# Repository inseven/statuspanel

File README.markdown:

# StatusPanel

eInk desk calendar and status board

## Overview

StatusPanel is a modern take on the desk calendar. It shows you just what you need to know about your upcoming day, without the temptation of messages, social media feeds, or the other online distractions that come from checking your phone.

Content is curated through an iOS app, meaning your StatusPanel can show events from any of the calendars you have on your phone, without sharing that content to any third-party service.

### Content Sources

The StatusPanel iOS app has built-in support for a number of content sources:

- Calendar
- [London Underground](https://tfl.gov.uk/modes/tube/) (UK)
- [National Rail](https://www.nationalrail.co.uk) (UK)
- [ZenQuotes](https://zenquotes.io)

### Privacy

StatusPanel uses end-to-end encryption to ensure your data remains private to you. Keys exchanged directly between StatusPanel and your phone are used to encrypt all updates; no one but you can see your updates.

StatusPanel can optionally show a privacy image or redact content at the touch of a button if you're worried who might see your calendar.

### Getting StatusPanel

StatusPanel is an open source project in the fairly early stages of development. We're planning to submit our [iOS app](ios/README,markdown) to the app store in the coming months and would love to manufacture a small batch of PCBs to make it easy for people to assemble their own. (It's 2021 though, so that might take longer than usual.)

If you can't wait to try it out, have a little technical experience, and don't mind getting your hands dirty, check out the [device documentation](device/README.markdown) for part listings and PCB schematics. If something's not clear, please reach out; we're happy to help out where we can and always appreciate code and documentation [contributions](#contributing) big or small.

## Technical Details

### Components

StatusPanel comprises a number of different components:

- [Firmware](firmware/README.markdown)
- [Device](device/README.markdown)
- [iOS app](ios/README.markdown)
- [Service](service/README.markdown)

## Development

### Installing Dependencies

StatusPanel uses [Git Submodules](https://git-scm.com/book/en/v2/Git-Tools-Submodules), so before doing anything else, you'll need to do:

```bash
git submodule update --init --recursive
```

N.B. You'll also need to run this command if the submodules change.

Once your submodules are up-to-date, you can install the dependencies for all StatusPanel components using the `install-dependencies.sh` script:

```bash
scripts/install-dependencies.sh
```

This script installs all dependencies in the `.local` folder within the project root, does not require root, and should not impact your local machine configuration. Scripts that rely on these dependencies source the `scripts/environment.sh` script which configures the path at runtime.

## Contributing

We invite and welcome contributions! There's a pretty comprehensive list of [issues](https://github.com/inseven/statuspanel/issues) to get you started, and our documentation is always in need of some care and attention.

Please recognise StatusPanel is a labour of love, and be respectful of others in your communications. We will not accept racism, sexism, or any form of discrimination in our community.

## Licensing

StatusPanel is licensed under the MIT License (see [LICENSE](LICENSE)).

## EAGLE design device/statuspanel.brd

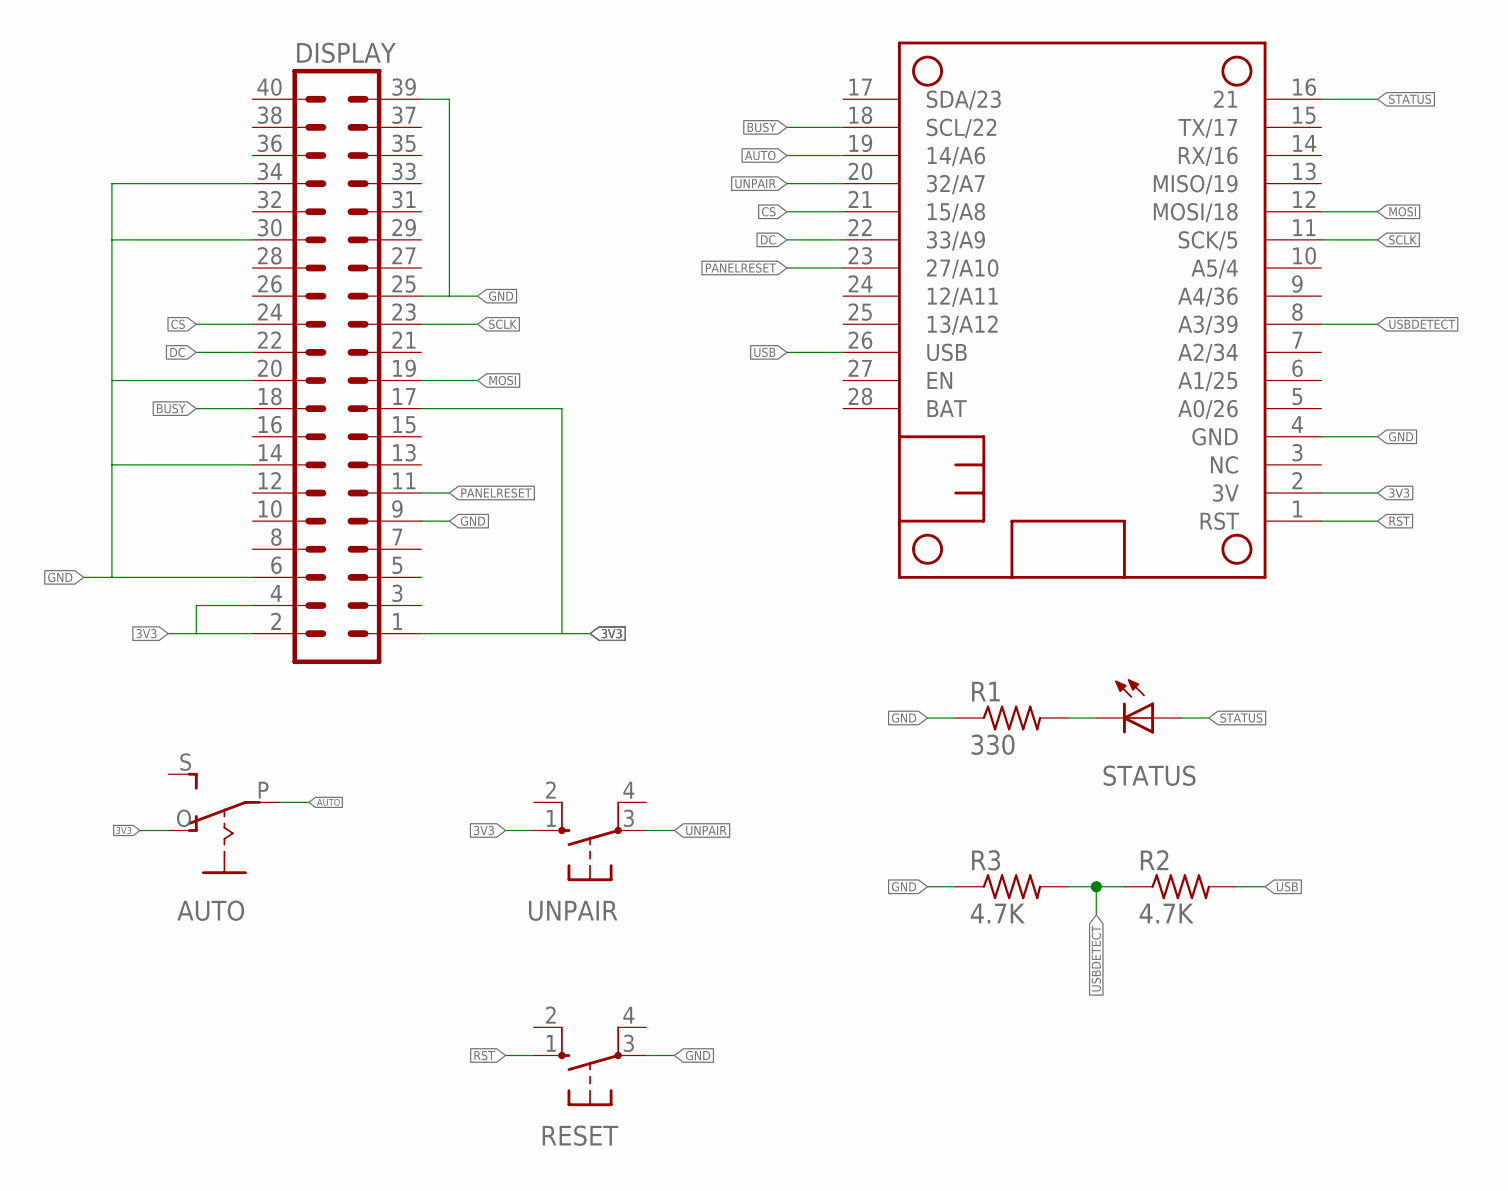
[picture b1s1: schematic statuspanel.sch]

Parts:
AUTO: EG1218S; EG1218
DISPLAY: MA20-2
HUZZAH32: HUZZAH32_NODIM; FEATHERWING_DIM
R1: 330; R0805
R2, R3: 4.7K; R0805
RESET: 10-XX; B3F-10XX
STATUS: LED3MM
UNPAIR: 10-XX; B3F-10XX

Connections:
3V3: AUTO.O, DISPLAY.1, DISPLAY.2, DISPLAY.4, DISPLAY.17, HUZZAH32.2 (3V), UNPAIR.1 (S)
AUTO: AUTO.P, HUZZAH32.19 (14/A6)
BUSY: DISPLAY.18, HUZZAH32.18 (SCL/22)
CS: DISPLAY.24, HUZZAH32.21 (15/A8)
DC: DISPLAY.22, HUZZAH32.22 (33/A9)
GND: DISPLAY.6, DISPLAY.9, DISPLAY.14, DISPLAY.20, DISPLAY.25, DISPLAY.30, DISPLAY.34, DISPLAY.39, HUZZAH32.4 (GND), R1.1, R3.1, RESET.3
MOSI: DISPLAY.19, HUZZAH32.12 (MOSI/18)
unnamed: R1.2, STATUS.K (C)
PANELRESET: DISPLAY.11, HUZZAH32.23 (27/A10)
RST: HUZZAH32.1 (RST), RESET.1 (S)
SCLK: DISPLAY.23, HUZZAH32.11 (SCK/5)
STATUS: HUZZAH32.16 (21), STATUS.A
UNPAIR: HUZZAH32.20 (32/A7), UNPAIR.3
USB: HUZZAH32.26 (USB), R2.2
USBDETECT: HUZZAH32.8 (A3/39), R2.1, R3.2

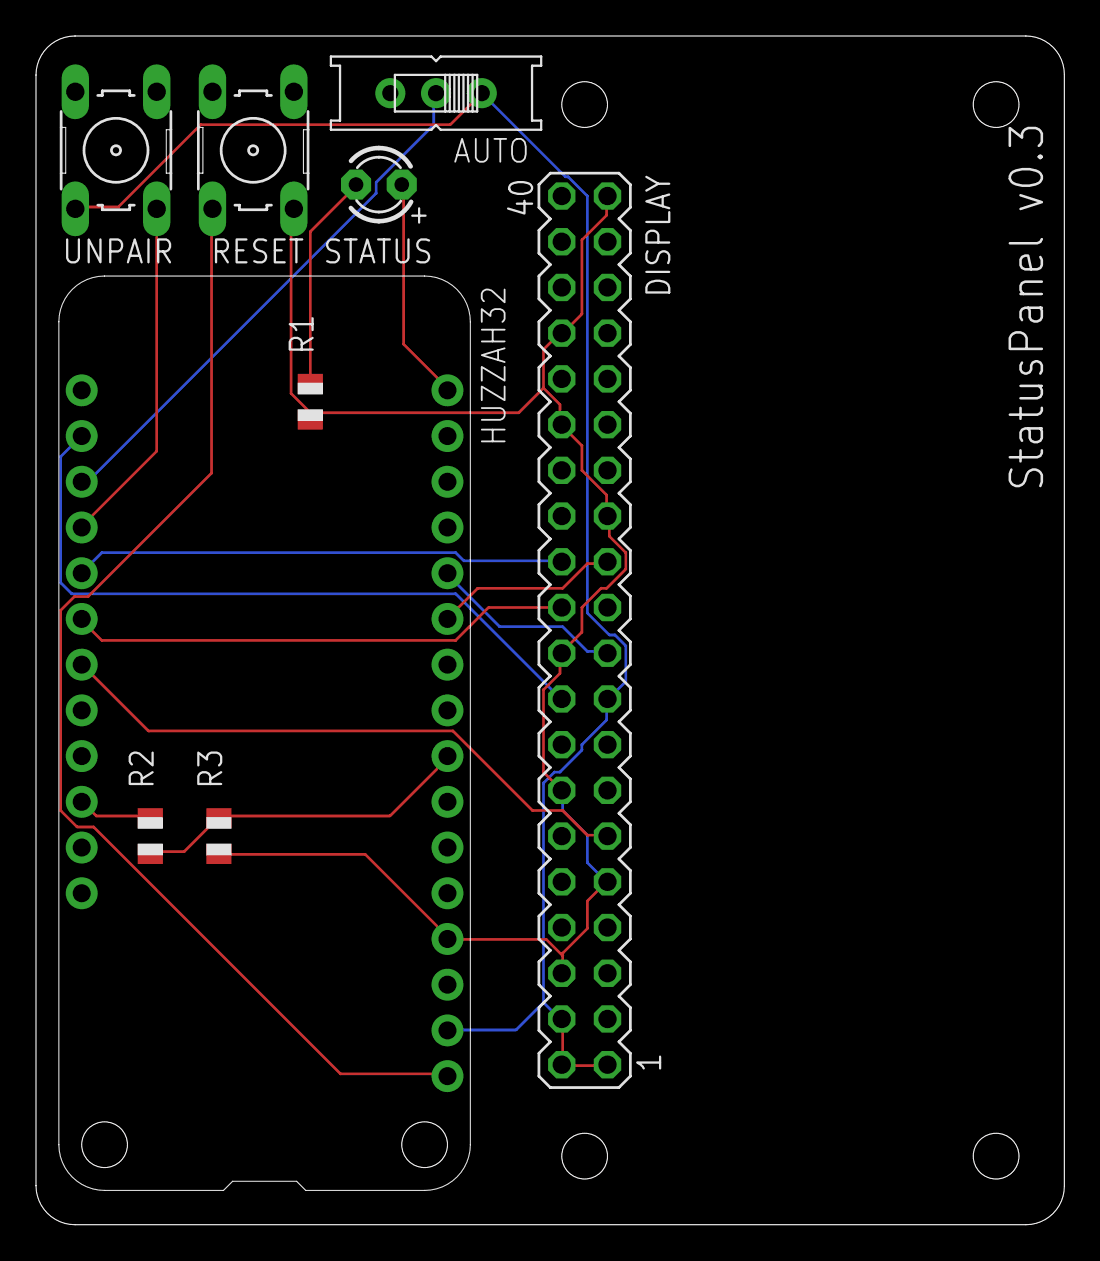
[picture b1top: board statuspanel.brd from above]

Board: 2 copper layers, 57.1 x 66.0 mm, 9 parts (0 on the bottom side), 15 nets.

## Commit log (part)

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2024-09-28 fix: Bump cryptography to address security issues
2024-09-28 fix: Bump cryptography to address security issues (#730)
2024-09-30 ci: Disable Raspberry Pi builds
    This change temporarily disables failing Raspberry Pi builds---I don't have time to figure out what's going wrong at the moment.
2024-10-01 ci: Disable Raspberry Pi builds (#732)
    This change temporarily disables failing Raspberry Pi builds---I don't
    have time to figure out what's going wrong at the moment.
2024-10-11 ci: Update distribution certificates
2024-10-11 Use the shared secrets.
2024-10-11 ci: Update distribution certificates (#733)
2024-11-12 fix: Allow non-main thread `Config` access
2024-11-12 fix: Allow non-main thread `Config` access (#735)
2024-11-22 fix: Dismiss the add device view controller on success or cancellation
2024-11-22 fix: Dismiss the add device view controller on success or cancellation (#736)
2025-01-10 ci: Address a non-sendable capture warning
2025-01-10 ci: Address a non-sendable capture warning (#737)
2025-01-18 ci: Use Python 3.10 for esp32 firmware builds
    This change uses `.tool-versions` via mise-en-place to pin Python to 3.10.11 as required by the esp32 nodemcu firmware builds.
2025-01-18 ci: Use Python 3.10 for esp32 firmware builds (#738)
    This change uses `.tool-versions` via mise-en-place to pin Python to
    3.10.11 as required by the esp32 nodemcu firmware builds.
2025-02-08 build: Bump the Python version to 3.12
2025-02-08 docs: Update the copyright to 2025
2025-02-08 docs: Update the copyright to 2025 (#740)
2025-02-22 Empty commit to trigger new build
2025-02-22 Empty commit to trigger new build (#741)
2025-02-22 fix: Update TestFlight build
2025-02-22 fix: Update TestFlight build (#742)
2025-04-02 ci: Disable esp32 firmware builds
    It looks like the version of `cmake` that now comes with Ubuntu has dropped support for the the declared format used by the esp32 `CMakeLists.txt` 🤦🏻‍♂️. This change simply disables the firmware buil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
2025-04-02 ci: Disable esp32 firmware builds (#743)
    It looks like the version of `cmake` that now comes with Ubuntu has
    dropped support for the the declared format used by the esp32
    `CMakeLists.txt` 🤦🏻‍♂️. This change simply disables the firmware builds
    as I don’t have the time to look into it at the moment.
2025-05-25 fix: Update TestFlight build (#744)
2025-08-26 fix: Update TestFlight build (#745)
2025-09-24 fix: 🎁 Build on Tahoe and target the iOS 26 SDK
2025-09-24 Install mise
2025-09-24 Remove separate pipenv install step
2025-09-24 Service builds still need pipenv?
2025-09-24 Python and node are unnecessary
2025-09-24 Update the Docker base image
2025-09-25 Don't change the Dockerfile unnecessary
2025-09-25 Use environment.sh in test-service.sh
2025-09-25 Source the correct location
2025-09-25 Clean up Python dependencies
2025-09-25 Fix-up tests with the new collections.abc
2025-09-25 collections.Callable
2025-09-25 fix: 🎁 Build on Tahoe and target the iOS 26 SDK (#746)
    This changes adopts a new approach to Python dependency management,
    bootstrapping with a local venv. It also relies on `mise` for installing
    local tooling and updates the website and service builds according.
2025-09-25 fix: 🎨 Update the about screen appearance for iOS 26
2025-09-25 fix: 🎨 Update the about screen appearance for iOS 26 (#747)
2025-09-26 ci: Always upload main builds to TestFlight
2025-09-26 Ensure we have an API key for the TestFlight upload
2025-09-26 Only do it on main
2025-09-26 Fix syntax error
2025-09-26 ci: Always upload main builds to TestFlight (#748)
2025-10-13 ci: Update provisioning profiles
2025-10-13 ci: Update provisioning profiles (#749)
2025-10-30 docs[website]: 🌑 Support Dark Mode
2025-10-30 docs[website]: 🌑 Support Dark Mode (#750)
2025-12-26 ci: Deploy using nginx
2025-12-26 Deploy PRs to staging
2025-12-26 ci: Deploy using nginx (#751)
2026-04-15 ci: Update GitHub Actions versions
    - `actions/checkout`: `v4` → `v6`
    - `actions/setup-node`: `v4` → `v6`
    - `jdx/mise-action`: `v2` → `v4`
    - `actions/upload-artifact`: `v4` → `v7`
    - `actions/download-artifact`: `v4` → `v8`
    - `actions/upload-pages-artifact`: `v3` → `v5`
2026-04-15 Update .tool-versions
2026-04-15 ci: Update GitHub Actions versions (#752)
    - `actions/checkout`: `v4` → `v6`
    - `actions/setup-node`: `v4` → `v6`
    - `jdx/mise-action`: `v2` → `v4`
    - `actions/upload-artifact`: `v4` → `v7`
    - `actions/download-artifact`: `v4` → `v8`
    - `actions/upload-pages-artifact`: `v3` → `v5`
